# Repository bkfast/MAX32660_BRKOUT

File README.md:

# MAX32660_BRKOUT
Simple Maxim MAX32660 Breakout PCB

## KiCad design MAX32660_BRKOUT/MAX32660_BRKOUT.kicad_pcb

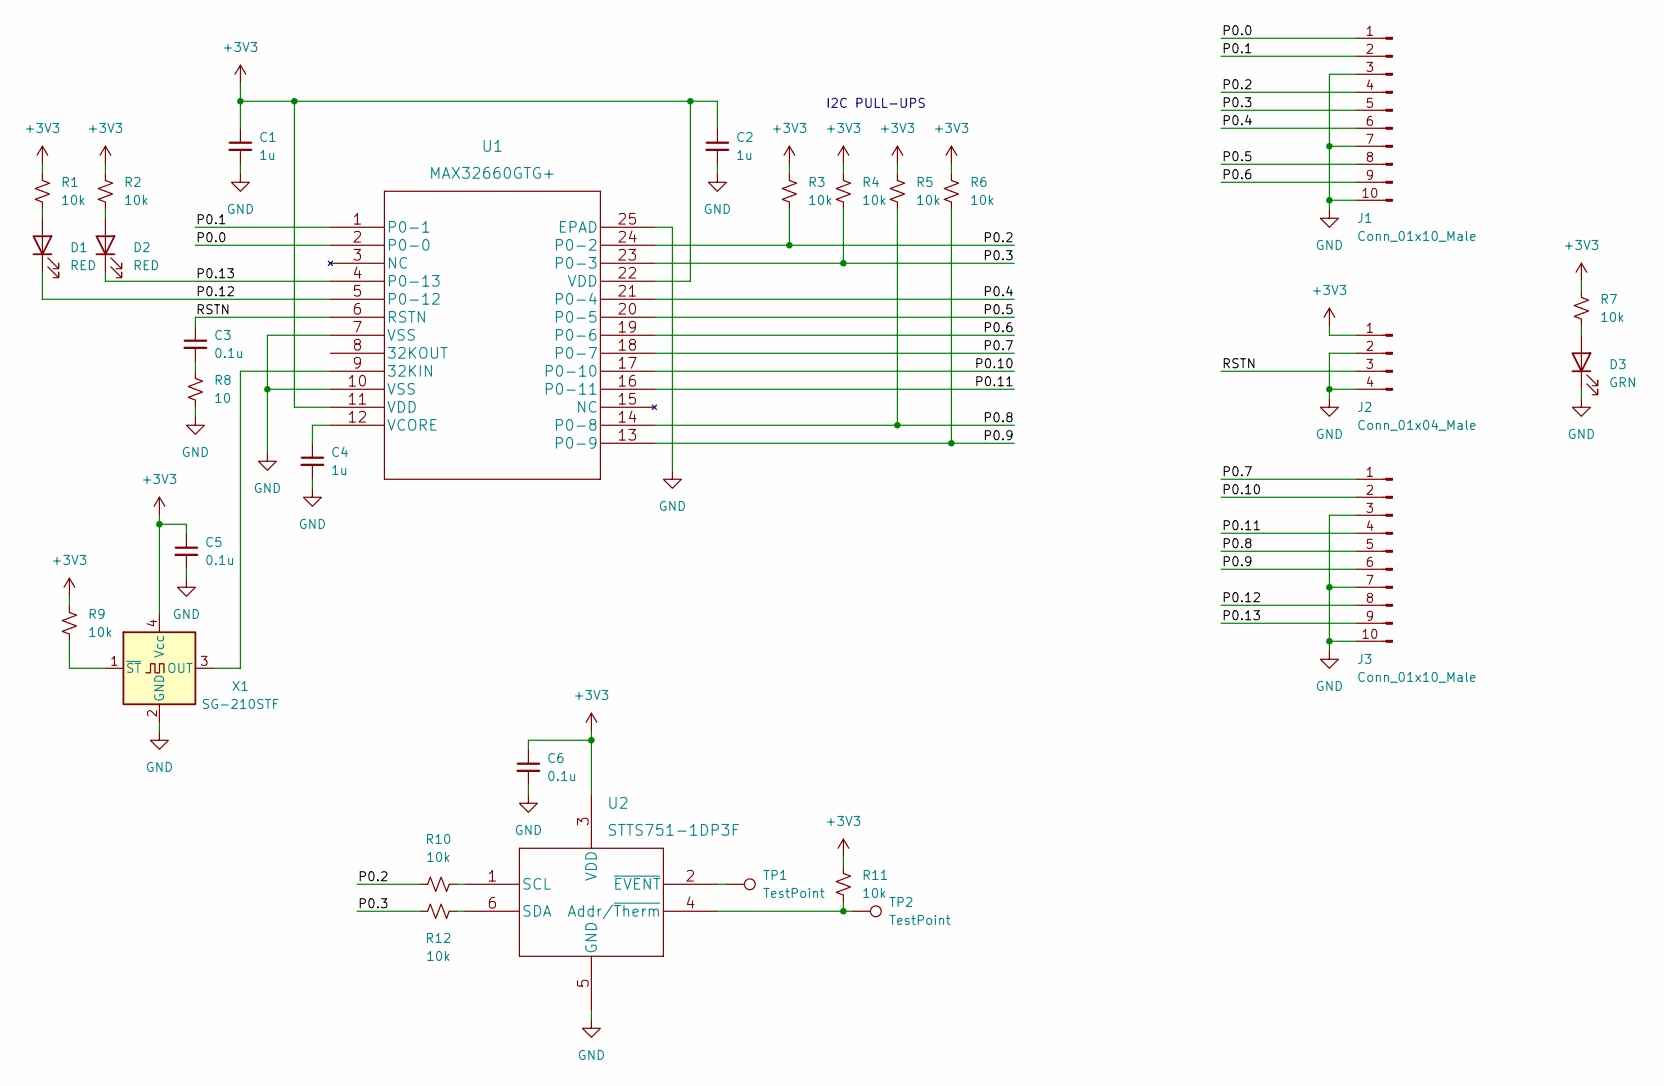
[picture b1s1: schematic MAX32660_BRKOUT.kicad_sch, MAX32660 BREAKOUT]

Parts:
C1, C2, C4: 1u; C_0402_1005Metric
C3, C5, C6: 0.1u; C_0402_1005Metric
D1, D2: RED; LED_0402_1005Metric
D3: GRN; LED_0402_1005Metric
J1, J3: Conn_01x10_Male; PinHeader_1x10_P2.54mm_Vertical
J2: Conn_01x04_Male; PinHeader_1x04_P2.54mm_Vertical
R1, R2, R3, R4, R5, R6, R7, R9, R10, R11, R12: 10k; R_0402_1005Metric
R8: 10; R_0402_1005Metric
TP1, TP2: TestPoint; TestPoint_Keystone_5015_Micro-Minature
U1: MAX32660GTG+; MAX32660GTG&plus_
U2: STTS751-1DP3F; UDFN-6L
X1: SG-210STF; Oscillator_SMD_SeikoEpson_SG210-4Pin_2.5x2.0mm

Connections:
+3V3: C1.1, C2.1, C5.1, C6.1, J2.1, R1.1, R2.1, R3.1, R4.1, R5.1, R6.1, R7.1, R9.1, R11.1, U1.11 (VDD), U1.22 (VDD), U2.3 (VDD), X1.4 (Vcc)
/P0.0: J1.1, U1.2 (P0-0)
/P0.1: J1.2, U1.1 (P0-1)
/P0.2: J1.4, R3.2, R10.1, U1.24 (P0-2)
/P0.3: J1.5, R4.2, R12.1, U1.23 (P0-3)
/P0.4: J1.6, U1.21 (P0-4)
/P0.5: J1.8, U1.20 (P0-5)
/P0.6: J1.9, U1.19 (P0-6)
/P0.7: J3.1, U1.18 (P0-7)
/P0.8: J3.5, R5.2, U1.14 (P0-8)
/P0.9: J3.6, R6.2, U1.13 (P0-9)
/P0.10: J3.2, U1.17 (P0-10)
/P0.11: J3.4, U1.16 (P0-11)
/P0.12: D1.1 (K), J3.8, U1.5 (P0-12)
/P0.13: D2.1 (K), J3.9, U1.4 (P0-13)
/RSTN: C3.1, J2.3, U1.6 (RSTN)
GND: C1.2, C2.2, C4.2, C5.2, C6.2, D3.1 (K), J1.3, J1.7, J1.10, J2.2, J2.4, J3.3, J3.7, J3.10, R8.2, U1.7 (VSS), U1.10 (VSS), U1.25 (EPAD), U2.5 (GND), X1.2 (GND)
unnamed: C3.2, R8.1
unnamed: C4.1, U1.12 (VCORE)
unnamed: D1.2 (A), R1.2
unnamed: D2.2 (A), R2.2
unnamed: D3.2 (A), R7.2
unnamed: R9.2, X1.1 (~ST)
unnamed: R10.2, U2.1 (SCL)
unnamed: R11.2, TP2.1, U2.4 (Addr/~Therm)
unnamed: R12.2, U2.6 (SDA)
unnamed: TP1.1, U2.2 (~EVENT)
unnamed: U1.9 (32KIN), X1.3 (OUT)

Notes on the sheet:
I2C PULL-UPS

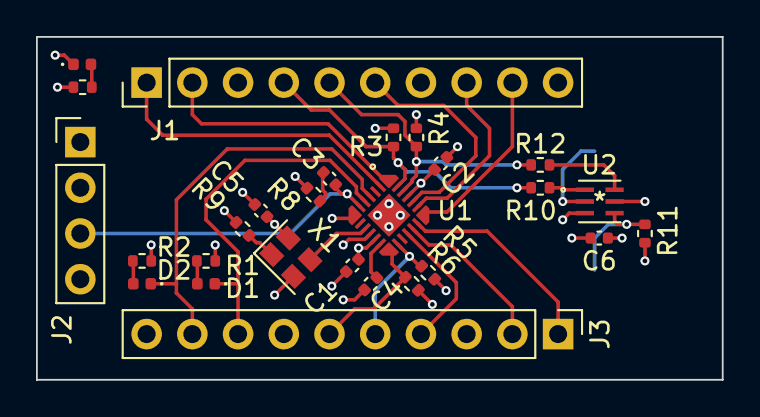
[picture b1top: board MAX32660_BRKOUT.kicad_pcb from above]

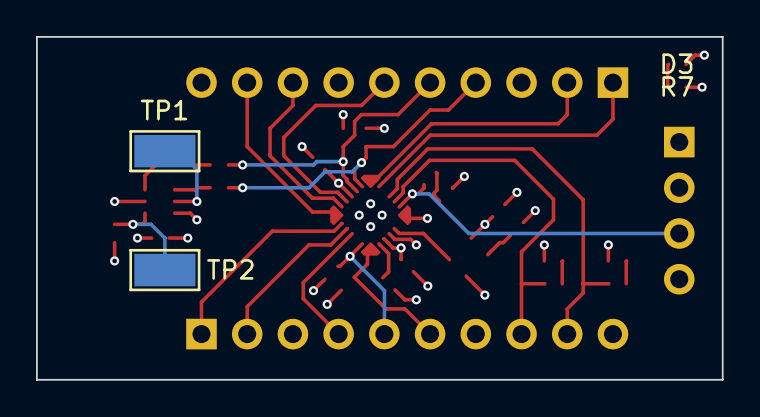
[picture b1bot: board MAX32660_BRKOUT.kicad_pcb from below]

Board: 4 copper layers, 38.1 x 19.0 mm, 29 parts (2 on the bottom side), 28 nets.

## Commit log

2022-03-31 Add to repo.

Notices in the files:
parts and their libraries:
Copyright 2021 Accelerated Designs. All rights reserved.
